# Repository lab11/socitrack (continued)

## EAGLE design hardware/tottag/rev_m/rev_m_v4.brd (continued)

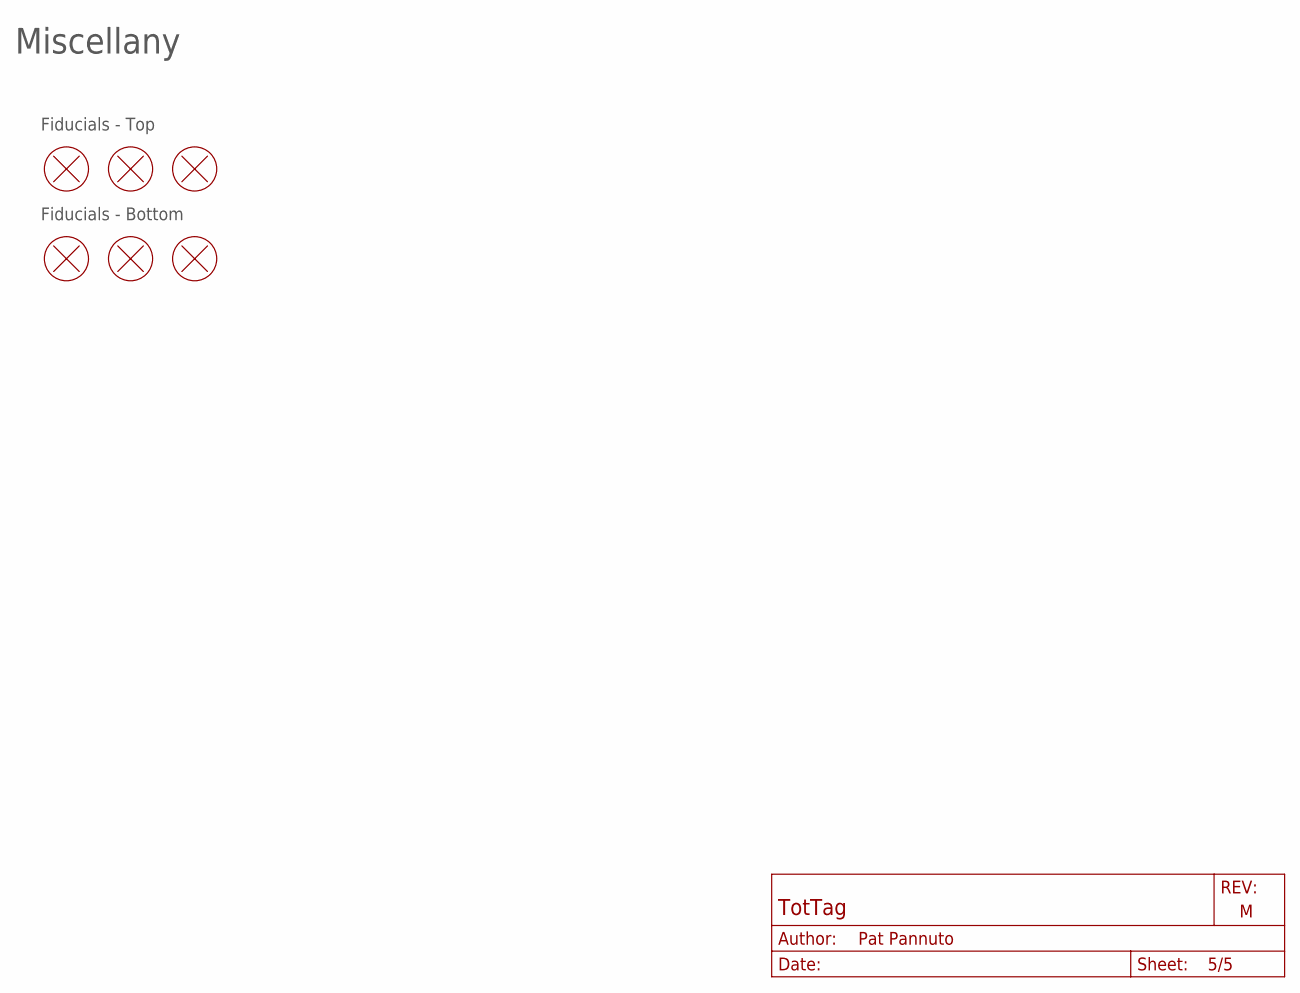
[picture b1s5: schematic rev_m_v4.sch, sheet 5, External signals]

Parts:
FD1, FD2, FD3, FD4, FD5, FD6: FIDUCIAL; FIDUCIAL_1MM-CU_2MM-MASK

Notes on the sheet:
Miscellany
Fiducials - Top
Fiducials - Bottom

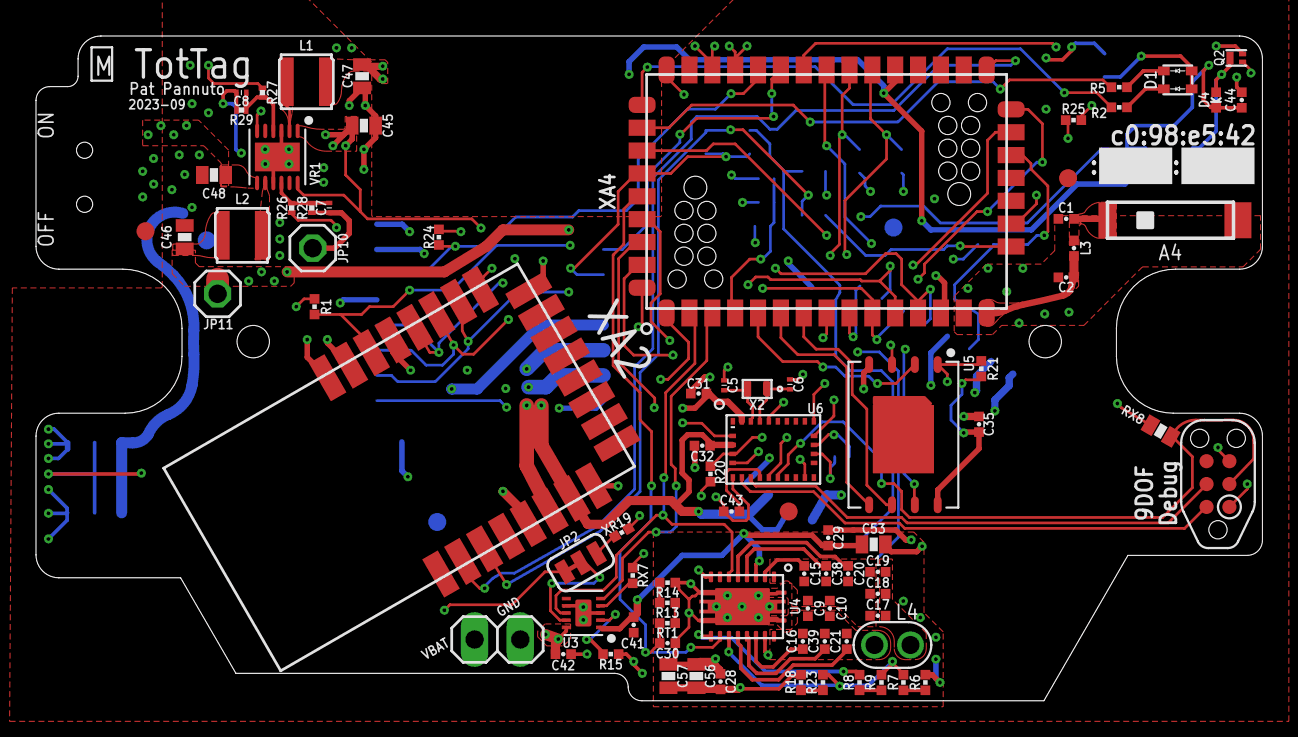
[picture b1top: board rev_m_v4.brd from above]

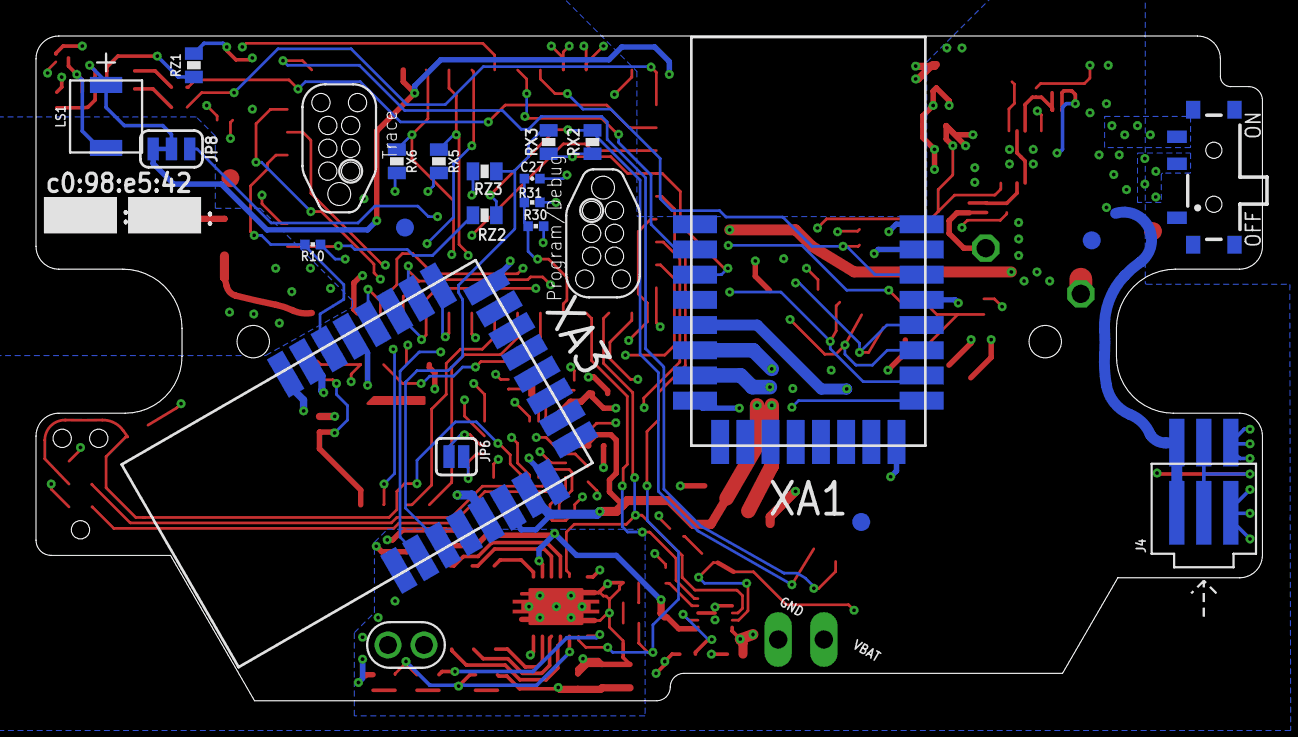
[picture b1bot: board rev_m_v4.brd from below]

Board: 4 copper layers, 68.1 x 36.9 mm, 103 parts (21 on the bottom side), 82 nets.

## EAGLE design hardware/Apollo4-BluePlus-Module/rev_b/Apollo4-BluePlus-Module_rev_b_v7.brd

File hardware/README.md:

Hardware
========

TotTag Gen 2 (2023-present)
---------------------------

- `rev_i` is a fairly complete overhaul of the TotTag platform, shedding
many of the legacy IC selections from the long design history of this project
(some traced back to the original 2015 PolyPoint board).

   - The most significant changes are moving from a dual-MCU design to a single MCU,
based around the Ambiq Apollo4 family of chips, and upgrading to the newer
generation UWB transciever, ~~Decawave~~ Qorvo's DW3000 family.

   - `rev_i` is in many ways a first revision of a new board.

- `rev_k` fixed most of the major flaws in from `rev_i`, but introduced new
problems around the DW3000.

- `rev_l` hedged around continued DW3000 issues and replaced the integrated
design with three copies of Qorvo's pre-fab module. This is a temporary
patch to get working systems with the new transciever more quickly to enable
scale-up.

- `rev_m` has only trivial, cosmetic fixes over `rev_l`.

- `rev_n` (in progress) removes the pre-fab UWB modules, and returns to the
integrated UWB design, which re-opens access to antenna diversity and the
improved robustness of ranging performance.

TotTag Gen 1 (2020-2023)
------------------------

Revisions of the original TotTags from the SociTrack project that focused on
the deployability, scaling, and robustness of the caregiver-infant interaction
tracking application.

This resulted in a more tightly integrated design as well as one more
aggressively geared towards a "wireless only" approach to ease device
management at-scale.

For more details, see the documentation in the [tottag folder](tottag/).

SociTrack (and TotTag Gen 0) (2017-2020)
----------------------------------------

The SociTrack system consists of a single PCB which integrates both an
application board and a SquarePoint module. SquarePoint is available from the
[*Lab11 EAGLE* library](https://github.com/lab11/eagle) as a design block
(check version number).

The original tottags (i.e., rev_c and rev_d) follow this more modularized
design, keeping SociTrack's components as cleanly separable features, but
integrating into a single PCB dual microcontrollers and enhanced functionality
such as SD card logging, accelerometer information, USB connectivity, wireless
charging, debugging ports, and LEDs, as well as battery voltage sensing.

PolyPoint (2015) and SurePoint (2016-2017)
------------------------------------------

The PolyPoint system consists of several PCBs centered around TriPoint, the core
UWB ranging module.

1. **TriPoint**: A triangular module which contains all of the necessary hardware
for utilizing a DecaWave DW1000 UWB radio. It has castellated headers so it can
be soldered onto a carrier board to add indoor localization functionality to any
device.

2. **TriTag**: A portable carrier board designed to be used as an indoor
localization tag. Contains TriPoint on one side and a BLE radio on the other.

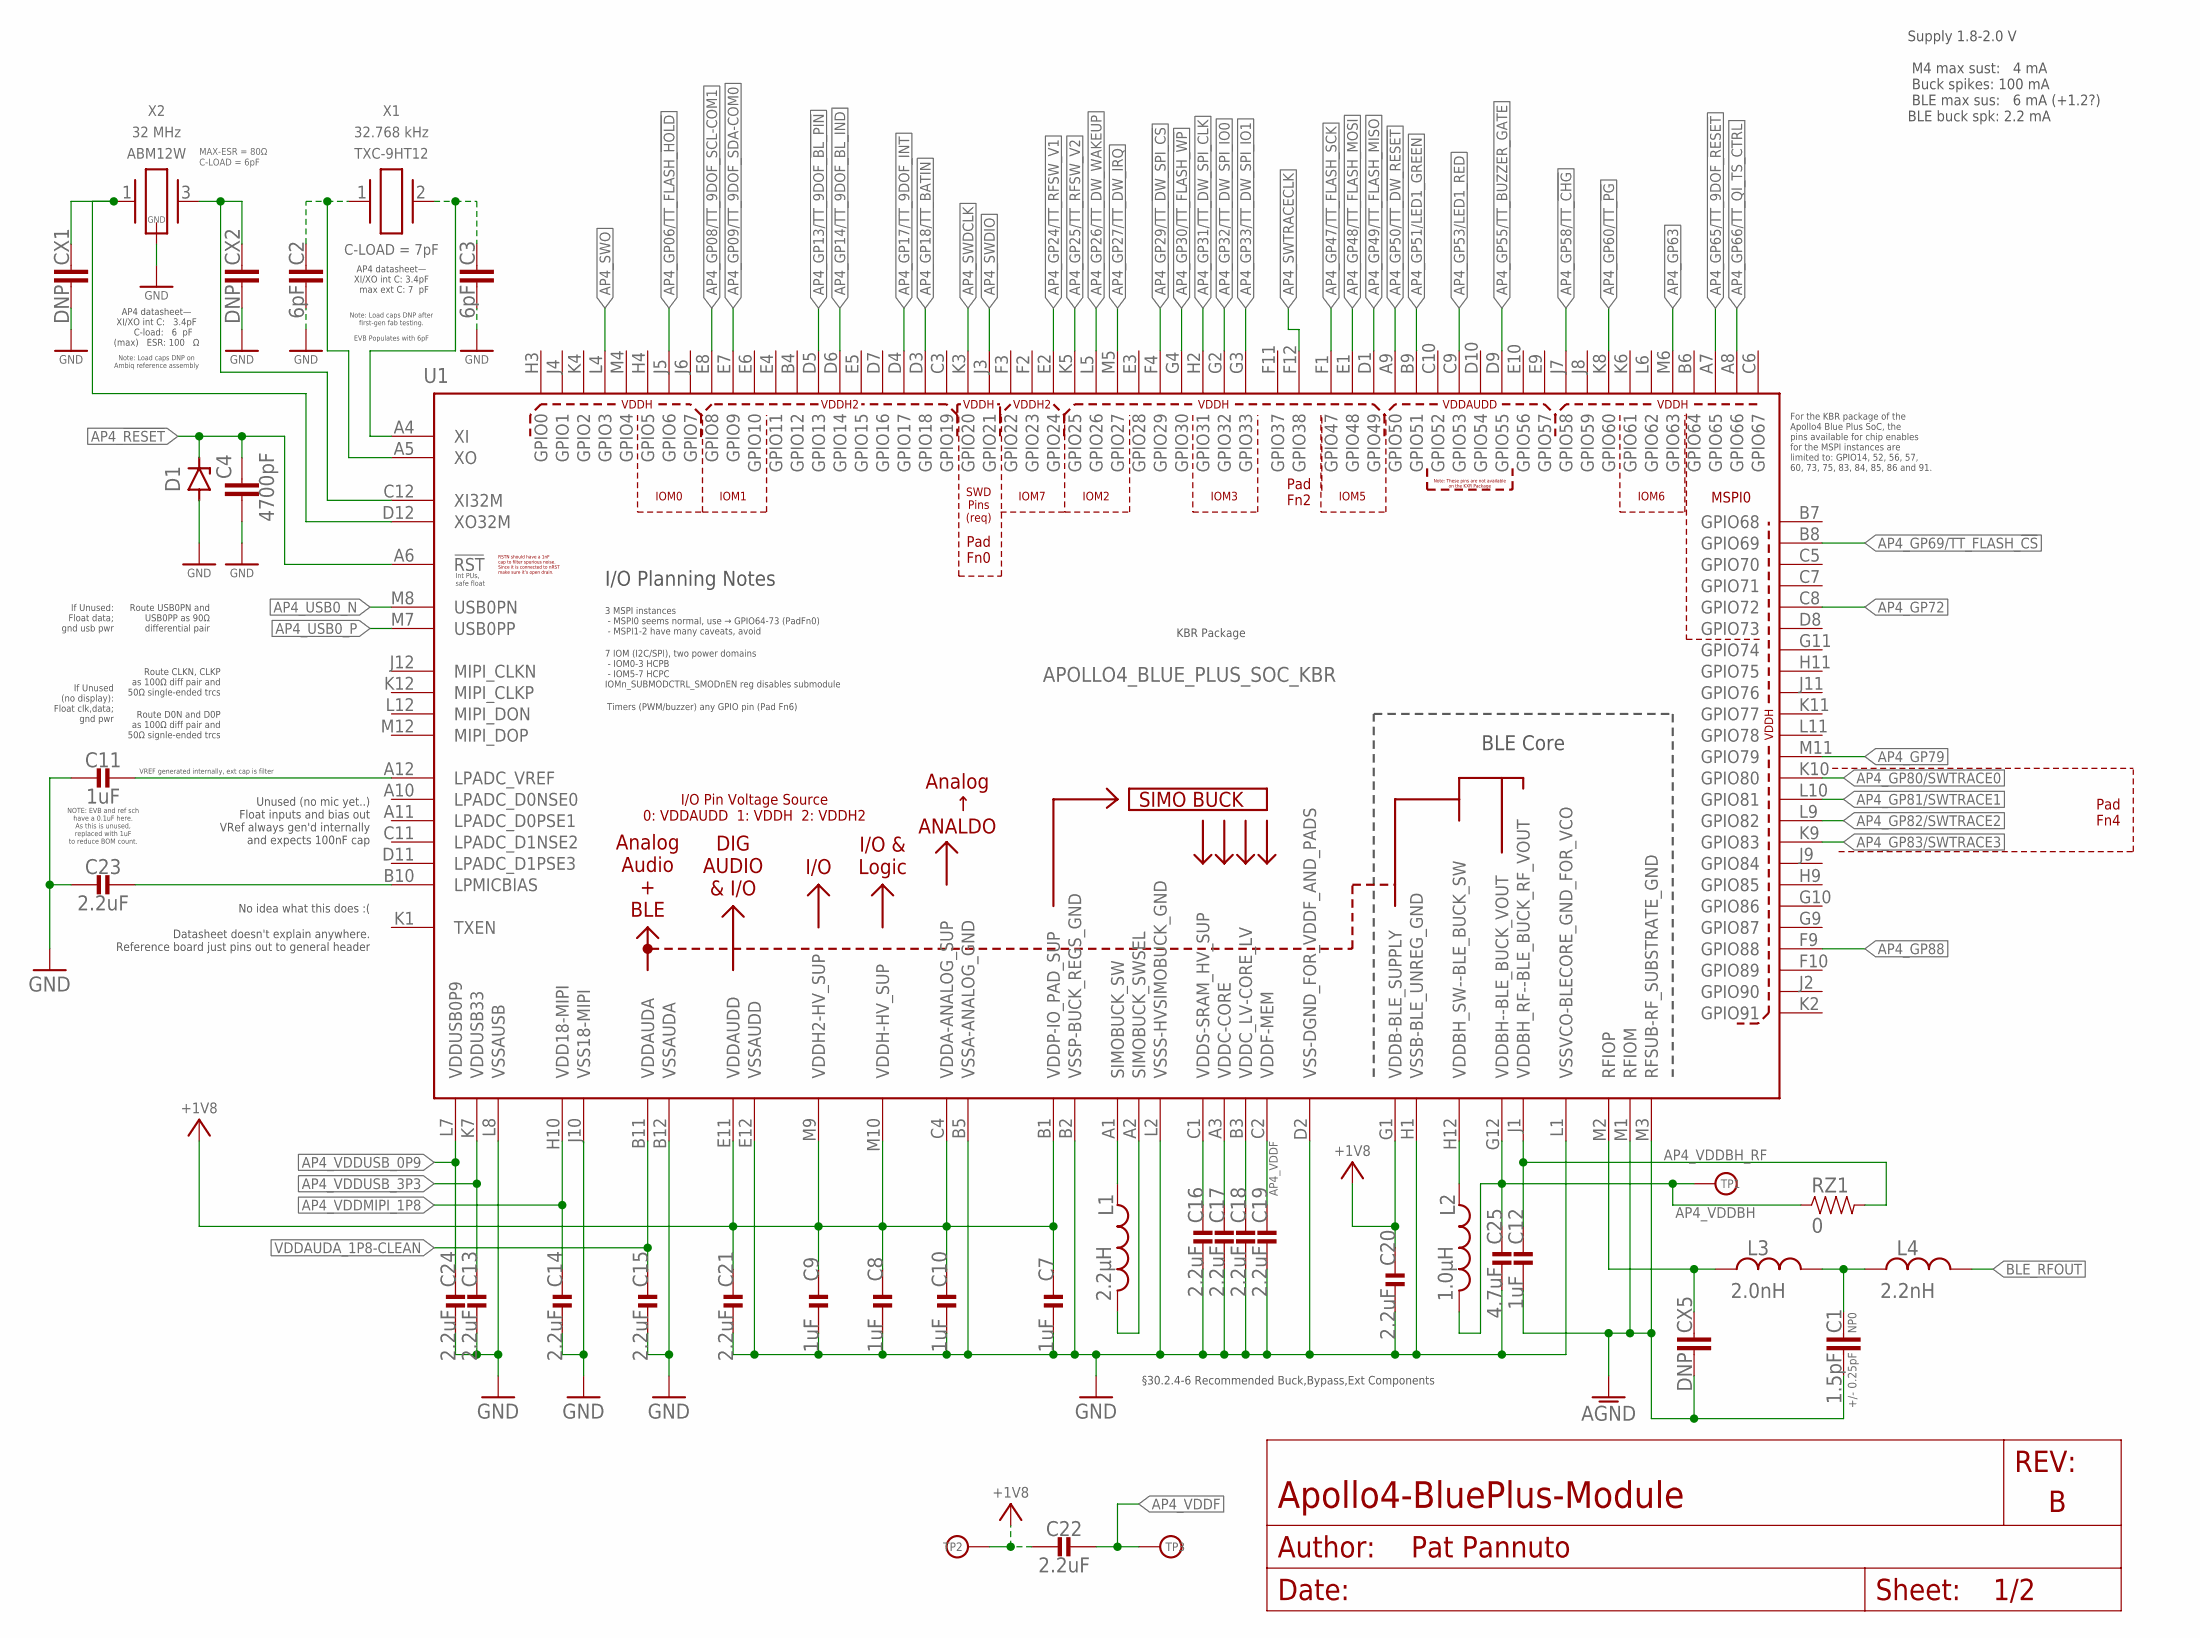
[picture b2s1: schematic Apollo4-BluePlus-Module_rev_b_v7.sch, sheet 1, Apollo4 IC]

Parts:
C1: 1.5pF; CAPC1005X60; TOLERANCE +/- 0.25pF; MPN C0402C159C5GAC7867
C2, C3: 6pF; CAPC1005X60; MPN GCM1555C1H6R0BA16D
C4: 4700pF; CAPC1005X60; MPN KGM05AR71E472KH
C7, C8, C9, C10, C11, C12: 1uF; 0201_CAP; MPN GRM033R61A105ME44D
C13, C14, C15, C16, C17, C18, C19, C20, C21, C22, C23, C24: 2.2uF; 0201_CAP; MPN GRM033R61A225KE47D
C25: 4.7uF; 0402_CAP; MPN CL05A475MP5NRNC
CX1, CX2, CX5: DNP; CAPC1005X60
D1: ZENER; SODFL1608X70; MPN PESD5V0X1UB,135
L1: 2.2µH; 0805_CAP; MPN DFE201210U-2R2M=P2
L2: 1.0µH; 0603_CAP; MPN DFE18SAN1R0ME0L
L3: 2.0nH; INDC1006X60N; TOLERANCE +/- 0.1 nH; MPN CTTF0402F-2N0B
L4: 2.2nH; INDC1006X60N; TOLERANCE +/- 0.1 nH; MPN CTTF0402F-2N2B
RZ1: 0; 0402_RES; MPN RMCF0402ZT0R00
TP1: VDDBH; PAD.03X.03
TP2: VDDP; PAD.03X.03
TP3: VDDF; PAD.03X.03
U1: APOLLO4_BLUE_PLUS_SOC_KBR; APOLLO4_BLUE_SOC_BGA
X1: TXC-9HT12; MPN 9HT12-32.768KDZY-T
X2: ABM12W; MPN ABM12W-32.0000MHZ-6-D1X-T3

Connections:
+1V8: C7.P$1 (1), C8.P$1 (1), C9.P$1 (1), C10.P$1 (1), C20.P$1 (1), C21.P$1 (1), C22.P$2 (2), TP2.P$1, U1.B1 (VDDP-IO_PAD_SUP), U1.C4 (VDDA-ANALOG_SUP), U1.E11 (VDDAUDD), U1.G1 (VDDB-BLE_SUPPLY), U1.M9 (VDDH2-HV_SUP), U1.M10 (VDDH-HV_SUP); also elsewhere on the board
AGND: C1.2, C12.P$2 (2), CX5.2, U1.M1 (RFIOM), U1.M3 (RFSUB-RF_SUBSTRATE_GND); also elsewhere on the board
AP4_!RESET: C4.1, D1.1 (C), U1.A6 (!RST); also elsewhere on the board
AP4_GP06/TT_FLASH_!HOLD: U1.J5 (GPIO6); also elsewhere on the board
AP4_GP08/TT_9DOF_SCL-COM1: U1.E8 (GPIO8); also elsewhere on the board
AP4_GP09/TT_9DOF_SDA-COM0: U1.E7 (GPIO9); also elsewhere on the board
AP4_GP13/TT_9DOF_!BL_PIN: U1.D5 (GPIO13); also elsewhere on the board
AP4_GP14/TT_9DOF_BL_IND: U1.D6 (GPIO14); also elsewhere on the board
AP4_GP17/TT_9DOF_INT: U1.D4 (GPIO17); also elsewhere on the board
AP4_GP18/TT_BATIN: U1.D3 (GPIO18); also elsewhere on the board
AP4_GP24/TT_RFSW_V1: U1.E2 (GPIO24); also elsewhere on the board
AP4_GP25/TT_RFSW_V2: U1.K5 (GPIO25); also elsewhere on the board
AP4_GP26/TT_DW_WAKEUP: U1.L5 (GPIO26); also elsewhere on the board
AP4_GP27/TT_DW_IRQ: U1.M5 (GPIO27); also elsewhere on the board
AP4_GP29/TT_!DW_SPI_CS: U1.F4 (GPIO29); also elsewhere on the board
AP4_GP30/TT_FLASH_!WP: U1.G4 (GPIO30); also elsewhere on the board
AP4_GP31/TT_DW_SPI_CLK: U1.H2 (GPIO31); also elsewhere on the board
AP4_GP32/TT_DW_SPI_IO0: U1.G2 (GPIO32); also elsewhere on the board
AP4_GP33/TT_DW_SPI_IO1: U1.G3 (GPIO33); also elsewhere on the board
AP4_GP47/TT_FLASH_SCK: U1.F1 (GPIO47); also elsewhere on the board
AP4_GP48/TT_FLASH_MOSI: U1.E1 (GPIO48); also elsewhere on the board
AP4_GP49/TT_FLASH_MISO: U1.D1 (GPIO49); also elsewhere on the board
AP4_GP50/TT_!DW_RESET: U1.A9 (GPIO50); also elsewhere on the board
AP4_GP51/LED1_GREEN: U1.B9 (GPIO51); also elsewhere on the board
AP4_GP53/LED1_RED: U1.C9 (GPIO53); also elsewhere on the board
AP4_GP55/TT_BUZZER_GATE: U1.D9 (GPIO55); also elsewhere on the board
AP4_GP58/TT_!CHG: U1.J7 (GPIO58); also elsewhere on the board
AP4_GP60/TT_!PG: U1.K8 (GPIO60); also elsewhere on the board
AP4_GP63: U1.M6 (GPIO63); also elsewhere on the board
AP4_GP65/TT_9DOF_!RESET: U1.A7 (GPIO65); also elsewhere on the board
AP4_GP66/TT_QI_TS_CTRL: U1.A8 (GPIO66); also elsewhere on the board
AP4_GP69/TT_FLASH_!CS: U1.B8 (GPIO69); also elsewhere on the board
AP4_GP72: U1.C8 (GPIO72); also elsewhere on the board
AP4_GP79: U1.M11 (GPIO79); also elsewhere on the board
AP4_GP80/SWTRACE0: U1.K10 (GPIO80); also elsewhere on the board
AP4_GP81/SWTRACE1: U1.L10 (GPIO81); also elsewhere on the board
AP4_GP82/SWTRACE2: U1.L9 (GPIO82); also elsewhere on the board
AP4_GP83/SWTRACE3: U1.K9 (GPIO83); also elsewhere on the board
AP4_GP88: U1.F9 (GPIO88); also elsewhere on the board
AP4_LPADC_VREF: C11.P$2 (2), U1.A12 (LPADC_VREF)
AP4_LPMICBIAS: C23.P$2 (2), U1.B10 (LPMICBIAS)
AP4_RFIOP: CX5.1, L3.1, U1.M2 (RFIOP)
AP4_SWDCLK: U1.K3 (GPIO20); also elsewhere on the board
AP4_SWDIO: U1.J3 (GPIO21); also elsewhere on the board
AP4_SWO: U1.L4 (GPIO3); also elsewhere on the board
AP4_SWTRACECLK: U1.F12 (GPIO38); also elsewhere on the board
AP4_USB0_N: U1.M8 (USB0PN); also elsewhere on the board
AP4_USB0_P: U1.M7 (USB0PP); also elsewhere on the board
AP4_VDDBH: C25.1, L2.2, RZ1.1, TP1.P$1, U1.G12 (VDDBH--BLE_BUCK_VOUT)
AP4_VDDBH_RF: C12.P$1 (1), RZ1.2, U1.J1 (VDDBH_RF--BLE_BUCK_RF_VOUT)
AP4_VDDBH_SW: L2.1, U1.H12 (VDDBH_SW--BLE_BUCK_SW)
AP4_VDDC: C17.P$1 (1), U1.A3 (VDDC-CORE)
AP4_VDDC_LV: C18.P$1 (1), U1.B3 (VDDC_LV-CORE_LV)
AP4_VDDF: C19.P$1 (1), C22.P$1 (1), TP3.P$1, U1.C2 (VDDF-MEM)
AP4_VDDMIPI_1P8: C14.P$1 (1), U1.H10 (VDD18-MIPI); also elsewhere on the board
AP4_VDDS: C16.P$1 (1), U1.C1 (VDDS-SRAM_HV_SUP)
AP4_VDDUSB_0P9: C24.P$1 (1), U1.L7 (VDDUSB0P9); also elsewhere on the board
AP4_VDDUSB_3P3: C13.P$1 (1), U1.K7 (VDDUSB33); also elsewhere on the board
AP4_XI: C3.1, U1.A4 (XI), X1.2
AP4_XI32M: CX2.1, U1.C12 (XI32M), X2.3 (2)
AP4_XO: C2.1, U1.A5 (XO), X1.1
AP4_XO32M: CX1.1, U1.D12 (XO32M), X2.1
BLE_RFOUT: L4.2; also elsewhere on the board
GND: C2.2, C3.2, C4.2, C7.P$2 (2), C8.P$2 (2), C9.P$2 (2), C10.P$2 (2), C11.P$1 (1), C13.P$2 (2), C14.P$2 (2), C15.P$2 (2), C16.P$2 (2), C17.P$2 (2), C18.P$2 (2), C19.P$2 (2), C20.P$2 (2), C21.P$2 (2), C23.P$1 (1), C24.P$2 (2), C25.2, CX1.2, CX2.2, D1.2 (A), U1.B2 (VSSP-BUCK_REGS_GND), U1.B5 (VSSA-ANALOG_GND), U1.B12 (VSSAUDA), U1.D2 (VSS-DGND_FOR_VDDF_AND_PADS), U1.E12 (VSSAUDD), U1.H1 (VSSB-BLE_UNREG_GND), U1.J10 (VSS18-MIPI), U1.L1 (VSSVCO-BLECORE_GND_FOR_VCO), U1.L2 (VSSS-HVSIMOBUCK_GND), U1.L8 (VSSAUSB), X2.2 (GND), X2.4 (GND); also elsewhere on the board
unnamed: C1.1, L3.2, L4.1
SIMOBUCK_SW: L1.P$1 (1), U1.A1 (SIMOBUCK_SW)
SIMOBUCK_SWSEL: L1.P$2 (2), U1.A2 (SIMOBUCK_SWSEL)
VDDAUDA_1P8-CLEAN: C15.P$1 (1), U1.B11 (VDDAUDA); also elsewhere on the board

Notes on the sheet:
Supply 1.8-2.0 V M4 max sust: 4 mA Buck spikes: 100 mA BLE max sus: 6 mA (+1.2?) BLE buck spk: 2.2 mA
Note: Load caps DNP on Ambiq reference assembly
Int PUs, safe float
If Unused: Float data; gnd usb pwr
If Unused (no display): Float clk,data; gnd pwr
Unused (no mic yet..) Float inputs and bias out VRef always gen'd internally and expects 100nF cap
No idea what this does :( Datasheet doesn't explain anywhere. Reference board just pins out to general header
I/O Planning Notes
3 MSPI instances - MSPI0 seems normal, use → GPIO64-73 (PadFn0) - MSPI1-2 have many caveats, avoid
7 IOM (I2C/SPI), two power domains - IOM0-3 HCPB - IOM5-7 HCPC IOMn_SUBMODCTRL_SMODnEN reg disables submodule
MSPI0
IOM0
IOM1
Timers (PWM/buzzer) any GPIO pin (Pad Fn6)
KBR Package
For the KBR package of the Apollo4 Blue Plus SoC, the pins available for chip enables for the MSPI instances are limited to: GPIO14, 52, 56, 57, 60, 73, 75, 83, 84, 85, 86 and 91.
§30.2.4-6 Recommended Buck,Bypass,Ext Components
SWD Pins (req)
VREF generated internally, ext cap is filter
IOM3
AP4 datasheet— XI/XO int C: 3.4pF max ext C: 7 pF
AP4 datasheet— XI/XO int C: 3.4pF C-load: 6 pF (max) ESR: 100 Ω
Pad Fn4
Pad Fn2
Pad Fn0
Note: Load caps DNP after first-gen fab testing. EVB Populates with 6pF
Route USB0PN and USB0PP as 90Ω differential pair
Route CLKN, CLKP as 100Ω diff pair and 50Ω single-ended trcs
Route D0N and D0P as 100Ω diff pair and 50Ω signle-ended trcs
NOTE: EVB and ref sch have a 0.1uF here. As this is unused, replaced with 1uF to reduce BOM count.
IOM2
IOM5
IOM6
IOM7

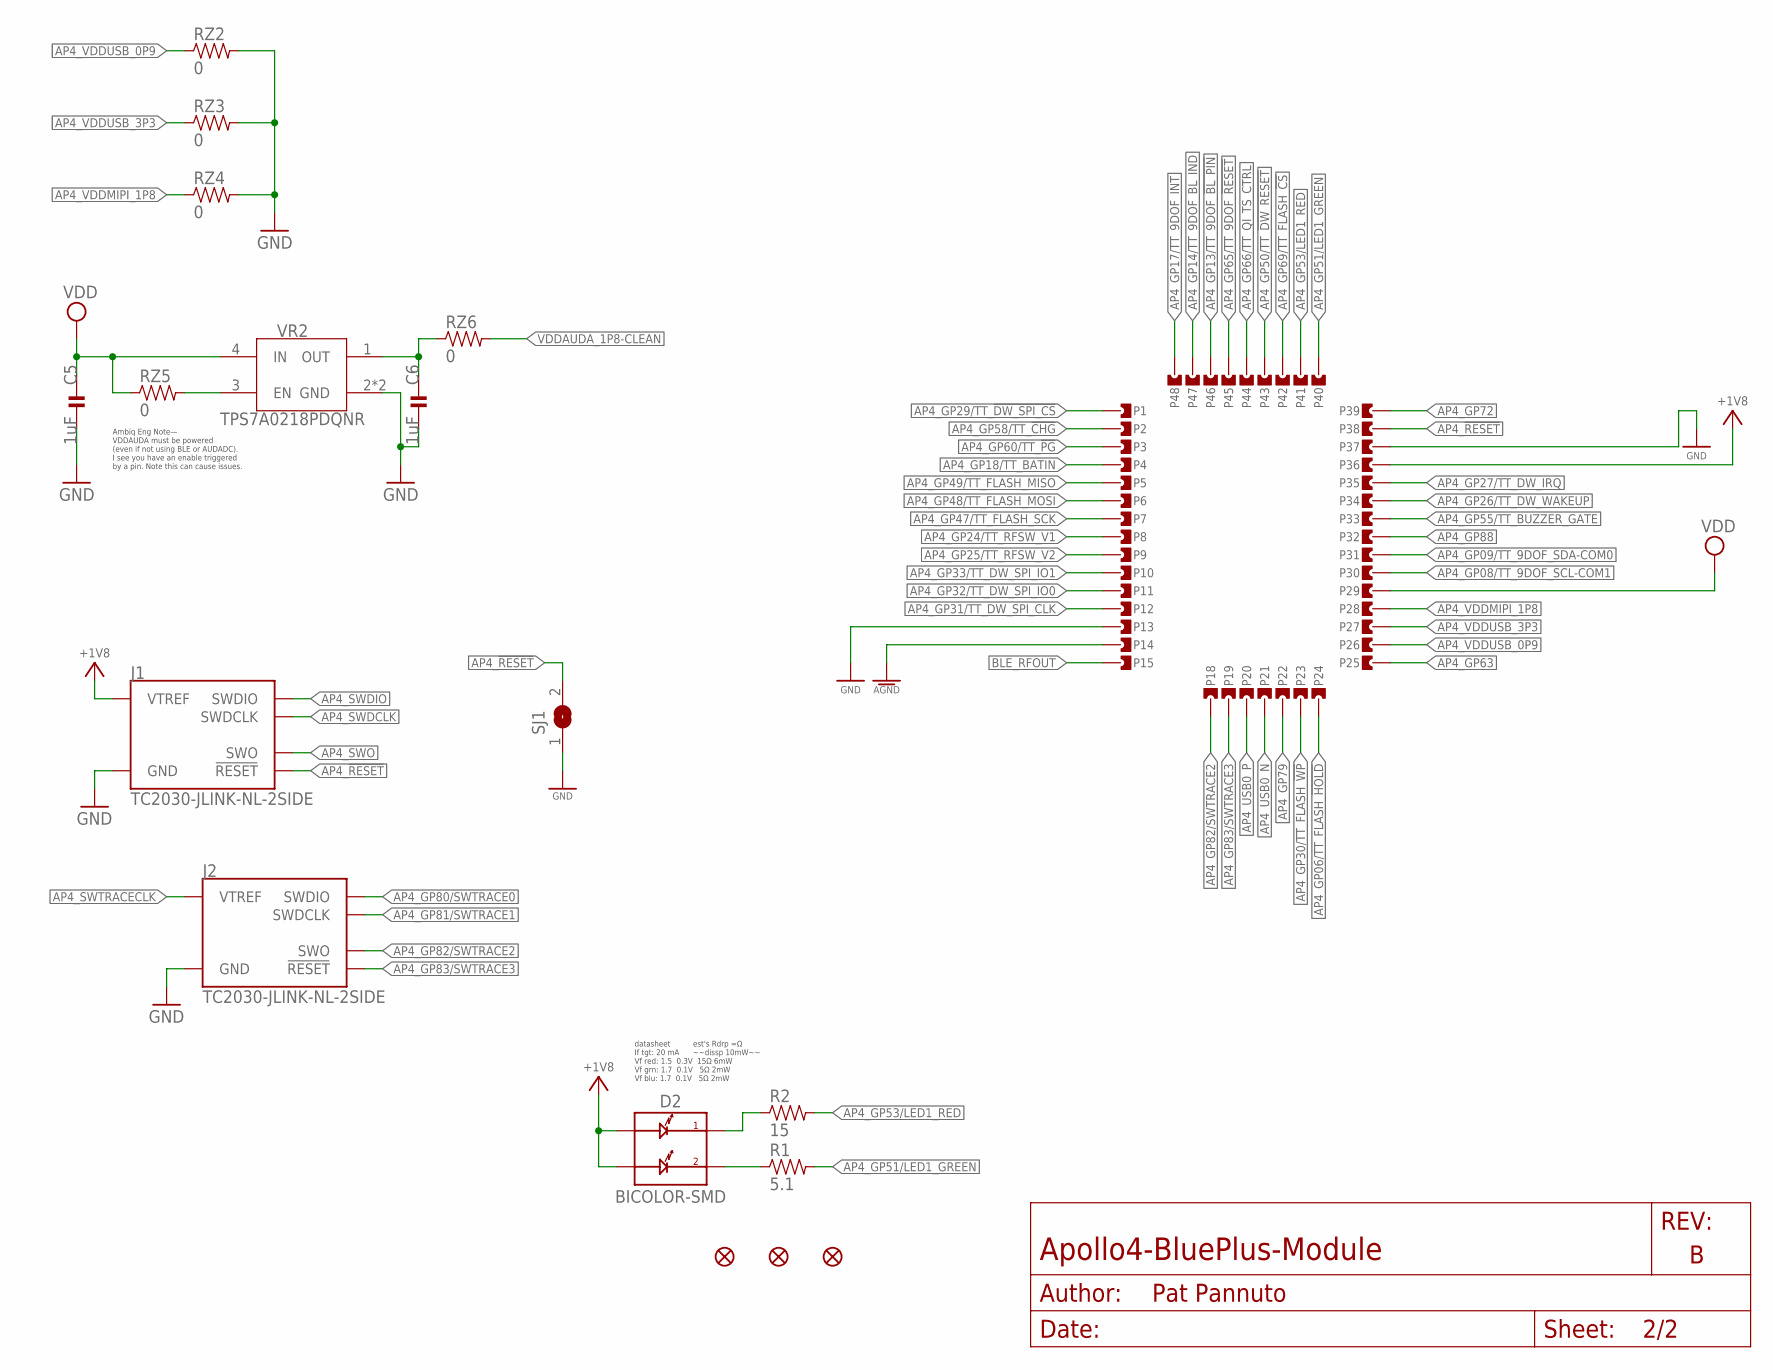
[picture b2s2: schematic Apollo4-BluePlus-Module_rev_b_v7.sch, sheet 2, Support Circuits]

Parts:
C5, C6: 1uF; 0201_CAP; MPN GRM033R61A105ME44D
D2: BICOLOR-SMD; LED-0606; MPN MCL0606FRD1GR1T
FD1, FD2, FD3: FIDUCIALUFIDUCIAL; FIDUCIAL-MICRO
J1, J2: TC2030-JLINK-NL-2SIDE; TC2030-IDC-NL-2SIDE
P1, P2, P3, P4, P5, P6, P7, P8, P9, P10, P11, P12, P13, P14, P15, P18, P19, P20, P21, P22, P23, P24, P25, P26, P27, P28, P29, P30, P31, P32, P33, P34, P35, P36, P37, P38, P39, P40, P41, P42, P43, P44, P45, P46, P47, P48: CASTELLATION4L; CASTELLATION-0.55MM_DRILL-4L
R1: 5.1; 0201_RES; MPN SR731HTTC5R10F
R2: 15; 0201_RES; MPN ERJ-1GNJ150C
RZ2, RZ3, RZ4, RZ5, RZ6: 0; 0402_RES; MPN RMCF0402ZT0R00
SJ1: SJ
VR2: TPS7A0218PDQNR; 4-XDFN-EP

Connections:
+1V8: D2.A1, D2.A2, J1.1 (VTREF), J1.B1 (VTREF), P36.P$1, P36.P$2, P36.P$3; also elsewhere on the board
AGND: P14.P$1, P14.P$2, P14.P$3; also elsewhere on the board
AP4_!RESET: J1.3 (!RESET), J1.B3 (!RESET), P38.P$1, P38.P$2, P38.P$3, SJ1.2; also elsewhere on the board
AP4_GP06/TT_FLASH_!HOLD: P24.P$1, P24.P$2, P24.P$3; also elsewhere on the board
AP4_GP08/TT_9DOF_SCL-COM1: P30.P$1, P30.P$2, P30.P$3; also elsewhere on the board
AP4_GP09/TT_9DOF_SDA-COM0: P31.P$1, P31.P$2, P31.P$3; also elsewhere on the board
AP4_GP13/TT_9DOF_!BL_PIN: P46.P$1, P46.P$2, P46.P$3; also elsewhere on the board
AP4_GP14/TT_9DOF_BL_IND: P47.P$1, P47.P$2, P47.P$3; also elsewhere on the board
AP4_GP17/TT_9DOF_INT: P48.P$1, P48.P$2, P48.P$3; also elsewhere on the board
AP4_GP18/TT_BATIN: P4.P$1, P4.P$2, P4.P$3; also elsewhere on the board
AP4_GP24/TT_RFSW_V1: P8.P$1, P8.P$2, P8.P$3; also elsewhere on the board
AP4_GP25/TT_RFSW_V2: P9.P$1, P9.P$2, P9.P$3; also elsewhere on the board
AP4_GP26/TT_DW_WAKEUP: P34.P$1, P34.P$2, P34.P$3; also elsewhere on the board
AP4_GP27/TT_DW_IRQ: P35.P$1, P35.P$2, P35.P$3; also elsewhere on the board
AP4_GP29/TT_!DW_SPI_CS: P1.P$1, P1.P$2, P1.P$3; also elsewhere on the board
AP4_GP30/TT_FLASH_!WP: P23.P$1, P23.P$2, P23.P$3; also elsewhere on the board
AP4_GP31/TT_DW_SPI_CLK: P12.P$1, P12.P$2, P12.P$3; also elsewhere on the board
AP4_GP32/TT_DW_SPI_IO0: P11.P$1, P11.P$2, P11.P$3; also elsewhere on the board
AP4_GP33/TT_DW_SPI_IO1: P10.P$1, P10.P$2, P10.P$3; also elsewhere on the board
AP4_GP47/TT_FLASH_SCK: P7.P$1, P7.P$2, P7.P$3; also elsewhere on the board
AP4_GP48/TT_FLASH_MOSI: P6.P$1, P6.P$2, P6.P$3; also elsewhere on the board
AP4_GP49/TT_FLASH_MISO: P5.P$1, P5.P$2, P5.P$3; also elsewhere on the board
AP4_GP50/TT_!DW_RESET: P43.P$1, P43.P$2, P43.P$3; also elsewhere on the board
AP4_GP51/LED1_GREEN: P40.P$1, P40.P$2, P40.P$3, R1.2; also elsewhere on the board
AP4_GP53/LED1_RED: P41.P$1, P41.P$2, P41.P$3, R2.2; also elsewhere on the board
AP4_GP55/TT_BUZZER_GATE: P33.P$1, P33.P$2, P33.P$3; also elsewhere on the board
AP4_GP58/TT_!CHG: P2.P$1, P2.P$2, P2.P$3; also elsewhere on the board
AP4_GP60/TT_!PG: P3.P$1, P3.P$2, P3.P$3; also elsewhere on the board
AP4_GP63: P25.P$1, P25.P$2, P25.P$3; also elsewhere on the board
AP4_GP65/TT_9DOF_!RESET: P45.P$1, P45.P$2, P45.P$3; also elsewhere on the board
AP4_GP66/TT_QI_TS_CTRL: P44.P$1, P44.P$2, P44.P$3; also elsewhere on the board
AP4_GP69/TT_FLASH_!CS: P42.P$1, P42.P$2, P42.P$3; also elsewhere on the board
AP4_GP72: P39.P$1, P39.P$2, P39.P$3; also elsewhere on the board
AP4_GP79: P22.P$1, P22.P$2, P22.P$3; also elsewhere on the board
AP4_GP80/SWTRACE0: J2.2 (SWDIO), J2.B2 (SWDIO); also elsewhere on the board
AP4_GP81/SWTRACE1: J2.4 (SWDCLK), J2.B4 (SWDCLK); also elsewhere on the board
AP4_GP82/SWTRACE2: J2.6 (SWO), J2.B6 (SWO), P18.P$1, P18.P$2, P18.P$3; also elsewhere on the board
AP4_GP83/SWTRACE3: J2.3 (!RESET), J2.B3 (!RESET), P19.P$1, P19.P$2, P19.P$3; also elsewhere on the board
AP4_GP88: P32.P$1, P32.P$2, P32.P$3; also elsewhere on the board
AP4_LED2_BLUE_COMM: D2.C1, R2.1
AP4_LED_RED_COMM: D2.C2, R1.1
AP4_SWDCLK: J1.4 (SWDCLK), J1.B4 (SWDCLK); also elsewhere on the board
AP4_SWDIO: J1.2 (SWDIO), J1.B2 (SWDIO); also elsewhere on the board
AP4_SWO: J1.6 (SWO), J1.B6 (SWO); also elsewhere on the board
AP4_SWTRACECLK: J2.1 (VTREF), J2.B1 (VTREF); also elsewhere on the board
AP4_USB0_N: P21.P$1, P21.P$2, P21.P$3; also elsewhere on the board
AP4_USB0_P: P20.P$1, P20.P$2, P20.P$3; also elsewhere on the board
AP4_VDDMIPI_1P8: P28.P$1, P28.P$2, P28.P$3, RZ4.1; also elsewhere on the board
AP4_VDDUSB_0P9: P26.P$1, P26.P$2, P26.P$3, RZ2.1; also elsewhere on the board
AP4_VDDUSB_3P3: P27.P$1, P27.P$2, P27.P$3, RZ3.1; also elsewhere on the board
BLE_RFOUT: P15.P$1, P15.P$2, P15.P$3; also elsewhere on the board
GND: C5.P$2 (2), C6.P$2 (2), J1.5 (GND), J1.B5 (GND), J2.5 (GND), J2.B5 (GND), P13.P$1, P13.P$2, P13.P$3, P37.P$1, P37.P$2, P37.P$3, RZ2.2, RZ3.2, RZ4.2, SJ1.1, VR2.2 (GND), VR2.PAD (GND); also elsewhere on the board
VDD: C5.P$1 (1), P29.P$1, P29.P$2, P29.P$3, RZ5.1, VR2.4 (IN)
VDDAUDA_1P8-CLEAN: RZ6.2; also elsewhere on the board
VR2_EN: RZ5.2, VR2.3 (EN)
VR2_OUT: C6.P$1 (1), RZ6.1, VR2.1 (OUT)

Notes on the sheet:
Ambiq Eng Note— VDDAUDA must be powered (even if not using BLE or AUDADC). I see you have an enable triggered by a pin. Note this can cause issues.
datasheet est's Rdrp =Ω If tgt: 20 mA ~~dissp 10mW~~ Vf red: 1.5 0.3V 15Ω 6mW Vf grn: 1.7 0.1V 5Ω 2mW Vf blu: 1.7 0.1V 5Ω 2mW

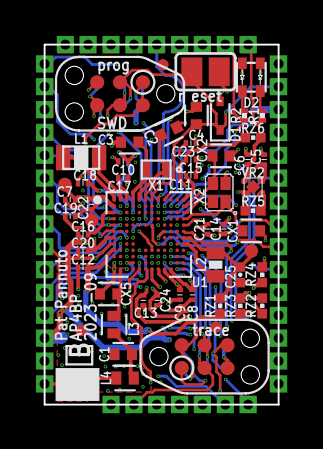
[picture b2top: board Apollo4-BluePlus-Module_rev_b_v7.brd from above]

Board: 4 copper layers, 13.0 x 20.0 mm, 101 parts (0 on the bottom side), 73 nets.

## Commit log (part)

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2023-12-08 Error check raw values before adding to logged data
2023-12-08 Allow manually specifying max range and start/end times
2023-12-11 Don't throw exception if log file processing can't fully complete due to a parsing error
2023-12-11 Disable IMU for full testing (should be reverted in future)
2023-12-12 Ignore devices with ASLEEP role
2023-12-12 Don't filter out duplicate TotTags from BLE scan results
2023-12-13 Add BLE hard reset functionality
2023-12-15 Ensure UID is a string when used as a label
2023-12-15 Re-enable use of IMU
2023-12-18 Update critical and nominal battery voltages
2023-12-18 Only start scheduler with a valid role
2023-12-21 Revert page index changes (wrong calculation)
2024-01-05 Bump pycryptodomex from 3.9.9 to 3.19.1 in /software/ersp
    Bumps [pycryptodomex](https://github.com/Legrandin/pycryptodome) from 3.9.9 to 3.19.1.
    - [Release notes](https://github.com/Legrandin/pycryptodome/releases)
    - [Changelog](https://github.com/Legrandin/pycryptodome/blob/master/Changelog.rst)
    - [Commits](https://github.com/Legrandin/pycryptodome/compare/v3.9.9...v3.19.1)
    ---
    updated-dependencies:
2024-01-08 Place top of stack at end of memory
2024-01-08 Add additional BLE WSF buffers
2024-01-08 Only calculate BLE DB hash upon first initialization
2024-01-08 Make storage task compilable for EVB
2024-01-08 Don't printf every LE meta sub event message
2024-01-08 Add "scan problem" timer to ensure that BLE actually starts scanning
2024-01-09 Add heap area
2024-01-09 Don't use storage in BLE+Ranging Test
2024-01-09 Can't use FreeRTOS delay in battery peripheral
2024-01-09 Don't deduplicate TotTag scan responses
2024-01-10 Only calculate BLE DB hash on first initialization
2024-01-11 Wait until full BLE reset before re-initializing upon error
2024-01-12 Update the instruction for provisioning on older devices
2024-01-12 Add 10s timer to check for BLE ADV errors
2024-01-12 Consolidate BLE error timers into one
2024-01-22 Bump pillow from 10.0.1 to 10.2.0 in /software/ersp
    Bumps [pillow](https://github.com/python-pillow/Pillow) from 10.0.1 to 10.2.0.
    - [Release notes](https://github.com/python-pillow/Pillow/releases)
    - [Changelog](https://github.com/python-pillow/Pillow/blob/main/CHANGES.rst)
    - [Commits](https://github.com/python-pillow/Pillow/compare/10.0.1...10.2.0)
    ---
    updated-dependencies:
2024-02-01 Re-enable IMU
2024-02-02 Ensure that no storage items are pushed from an ISR
2024-02-02 Let storage wait forever until not busy
2024-02-02 Fix storage - can't write page without erasing first
2024-02-02 Work with new storage implementation
2024-02-09 Add RX receive power test
2024-02-13 Only use one "debugging" definition
2024-02-16 Switch the active ranging radio to the top (single) module
2024-02-29 add interactive paired ranging plot
2024-02-29 add textbox to allow applying time offset to annotations
2024-03-01 Allow for ranging intervals other than 1s
2024-03-01 Keep BLE scanning if we are ranging as Master (to detect network collisions)
2024-03-05 Fix optimized code issue (FreeRTOS-based problem)
2024-03-08 Suppress pandas scientific notification to facilitate data examination
2024-03-18 Use RTC to timestamp all stored data
2024-04-03 Bump pillow from 10.2.0 to 10.3.0 in /software/ersp
    Bumps [pillow](https://github.com/python-pillow/Pillow) from 10.2.0 to 10.3.0.
    - [Release notes](https://github.com/python-pillow/Pillow/releases)
    - [Changelog](https://github.com/python-pillow/Pillow/blob/main/CHANGES.rst)
    - [Commits](https://github.com/python-pillow/Pillow/compare/10.2.0...10.3.0)
    ---
    updated-dependencies:
2024-04-16 print out error message when parsing the raw data
2024-04-27 Add function to retrieve daily ranging statistics
2024-04-27 Processing script parsing fixes
2024-04-29 Finalize time range download capabilities
2024-05-01 Create Bluetooth_Power_Calculator_v4.0.2.xlsx
    Add BLE Power Calculator doc
2024-05-01 Fix start/end timestamp in case they are out of experiment bounds
2024-05-08 print out BLE connection exception details in dashboard
2024-05-17 Fix display range in the visualizer
2024-06-05 Allow 2 max connections to allow Dashboard connection while BLE scanning
2024-06-07 fix bluetooth test
2024-06-08 allow disable the data ready interrupts
2024-06-12 add test_ble_range_imu
2024-06-12 Initial support for nonblocking I2C read
2024-06-17 Bump scikit-learn from 1.0.1 to 1.5.0 in /software/ersp
    Bumps [scikit-learn](https://github.com/scikit-learn/scikit-learn) from 1.0.1 to 1.5.0.
    - [Release notes](https://github.com/scikit-learn/scikit-learn/releases)
    - [Commits](https://github.com/scikit-learn/scikit-learn/compare/1.0.1...1.5.0)
    ---
    updated-dependencies:
    - dependency-name: scikit-learn
2024-06-18 add time diff test to RTC test
2024-06-19 BLE live imu data sketch
2024-06-21 only include live imu data BLE service when the _LIVE_IMU_DATA flag is set
2024-06-22 fix conditional inclusion for the _LIVE_IMU_DATA flag
2024-06-22 fix CCCD issue
2024-06-22 add flag for no battery callback
2024-06-22 Make it clear in dashboard that scheduling changes only apply to the current connected device
2024-06-22 add documentation for the dashboard and processing script
2024-06-23 add functionality to save imu raw data
2024-06-23 add a flag to just download everything
2024-06-24 Fix dashboard installation
2024-06-25 enable picking data from the multi-byte burst read
2024-06-25 add function to get on and off charger time
2024-06-25 Move IMU storage container into ifdef guards
2024-06-25 Add Dashboard requirements
2024-06-25 add doc for BNO055 firmware update
2024-06-25 Add storage ability to get actual number of log bytes
2024-06-25 First pass at RTT download script (needs help flushing)
2024-06-26 Transmit extra RTT packets to flush RTT buffer
2024-06-26 RTT Logfile download script updates
2024-06-26 Make log file dl end date inclusive
2024-06-26 Better timing-based download script
2024-06-27 Make the segger download available after remote switching
2024-06-27 remove obsolete compilation flag
2024-06-27 Add a script to remotely trigger segger download
2024-06-27 Fix deprecated datetime calls
2024-06-27 Reduce optimization level for better BLE stability
2024-06-28 Change datetime.UTC to timezone.utc for compatibility
2024-06-29 handle motion status change properly for BLOCKING imu
2024-07-01 Fix the utcfromtimestamp deprecation finally
2024-07-02 fix timezone interpretation for charging status plot
2024-07-15 add functions to parse IMU data
2024-07-16 add headers to loaded data
2024-07-17 Lots of IMU cleanup, merged block/nonblocking code
2024-07-18 Don't try to store or BLE write inside ISR context
2024-07-18 re-enable picking data for testing purpose
2024-07-18 Fully separate "test" raw IMU data from "app" typed data
2024-07-18 Update function defs for const correctness
2024-07-18 Print out IMU events from app_task_ranging
2024-07-18 Enable fusion mode for app
2024-07-18 Increase motion-detect sensitivity
2024-07-18 Ensure IMU data is stored at a max of 2Hz
2024-07-18 Don't force reboot in a loop if device is on charger
2024-07-19 simplify connection procedure to BNO055 chip
2024-07-19 update instructions for BNO055 firmware update
2024-07-23 ensure that the IMU is not repeatedly inited or deinited
2024-07-24 download everything with -D_TEST_IMU_DATA
2024-07-24 automate IMU data length calculation for data parser
2024-08-09 raise the IMU interrupts priority again for it to work during ranging
2024-08-11 Add relevant datasheets
2024-08-11 Add UWB continuous wave/frame test tools
2024-08-16 add draft rev n
2024-08-21 Add ability to store BLE scan results to logs
2024-08-21 Auto-reconnect/continue BLE download upon timeout
2024-08-21 Add script to parse PKL from raw TTG file (without ID labels)
2024-08-22 Fix BLE scan storage
2024-08-22 Add processing for BLE scan results
2024-08-28 Change Firmware Revision string to Git commit hash
2024-09-11 Change -fno-omit-frame-pointer flag since it was causing weird bugs
2024-09-23 bump candidate hw rev
2024-10-21 rev_n: Updates from DFM review
2024-10-21 add fab notes
2024-10-30 More timestamp search updates
2024-11-05 Allow downloading of full logs and restrict to <21 days
2024-11-05 Get ready with pinouts for revN
2024-11-05 Update storage peripheral to support new larger chip
2024-11-06 Update storage peripheral for new revN device
2024-11-13 rev_n: manufacturing fixes
    - Fix U2 footprint
    - Add tCream for S4
    - Fix AP4/9DOF SPI/I2C mux mismatch with SJ's
    - Removes RX9 and RZ12
    - Rename solder jumpers as SJ#
2024-11-13 rev_n: manufacturing update
    - Fix mask, cream for pads on S2, S3
2024-12-02 Always enable IMU BLE characteristic
2024-12-02 Update for new IMU chip
2024-12-12 Add new Flash memory datasheet
2024-12-12 Update Makefiles to default to revN
2024-12-12 Add YELLOW LED control for newer revisions
2024-12-12 Add delay after DW3000 driver probe failure to keep chip from becoming permanently inaccessible
2024-12-12 Make memory page size board-specific and configurable
2024-12-12 Fully working storage peripheral for revN
2025-01-17 Allow selecting antenna/channel in ranging power test
2025-01-17 Fix IMU init after reset + motion-detect results
2025-01-21 Add TinyUSB external lib to source code
2025-01-24 Prepare for revO
2025-01-24 Only allow TinyUSB to print if debugging enabled
2025-01-24 Add parameters to function definitions to make compiler happy
2025-02-04 disable BLE scanning result storage
2025-02-05 Fix weird storage issue where writing fails for no good reason
2025-02-13 Update pinout for Rev O
2025-02-13 Use external LNA for all antennas in Rev O
2025-02-14 rev_o: add fab files from CH
2025-02-19 wip across machines
2025-02-19 add debugging outputs
2025-02-19 rev_n: add fab files
2025-02-20 add instruction for updating the BLE firmware
2025-02-22 50Hz but double data each time
2025-02-22 50Hz batch size 2 real data (timestamp and raw acc included)
2025-02-26 Auto-update BLE FW when flashing (easy future upgrades)
2025-03-19 Sleep after reset to allow DW3000 probe to succeed
2025-03-20 Implement USB download functionality
2025-03-25 add more statistical calculations
2025-04-02 Remove support for revisions older than RevM
2025-04-02 Simplify ranging phase (make shorter)
2025-04-04 Add back DW presence checker for RevM
2025-04-04 Shorten IEEE 802.15.4 header
2025-04-04 Take lowest range as best estimate
2025-04-06 Calculate src addr from slot instead of transmitting
2025-04-06 Write to DW3000 xmit buffer incrementally to cut down on SPI times all at once
2025-04-06 Cannot take address of register variable
2025-04-07 Don't retry DW3000 SPI fails
2025-04-07 Actually use Kalman filters
2025-04-07 Unfortunately can't use 16-bit xfer ranges for now
2025-04-07 Fix RevM IMU accel reading call
2025-04-07 Allow preamble timeout during subscription phase
2025-04-22 Allow terminating deployment without destroying data
2025-04-22 Update SEGGER download script with new experiment details length
2025-05-12 doc: add AP4 Plus Errata
2025-05-13 rev_p: Initial to-fab files
2025-07-21 Update HW build revision to revP
2025-07-30 add comment to parse.py
2025-08-01 lower the ranging_radio test write freq for better signal visibility
2025-09-03 Add manufacturing validation tests
2025-09-03 Test all antennas in manufacturing test
2025-09-17 Finalize manufacturing test code
2025-09-17 Add actual manufacturing test scripts (should be zipped and sent)
2025-10-29 Add IMU processing to dashboard PKL conversion
2025-11-04 Enable IMU acceleration data storage when in motion
2025-12-02 hw: add rev P.2 design files (DRC updates for MacroFab)
2026-01-13 Finalize TotTag manufacturing testing
2026-01-15 Ensure deinit only happens if initialized
2026-02-26 Clarify firmware update instructions in README
    Updated the firmware flashing instructions to specify replacing BOARD_REV with the revision of the board being flashed.
2026-02-26 Fix formatting in firmware update instructions
2026-03-03 flush storage when USB-C is plugged in
